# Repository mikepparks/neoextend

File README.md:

# NEOExtend
Neo Geo/Supergun compatible breakouts for arcade controls.

# Description
This series of boards is intended to help arcade controller & fighting game stick builders create a compatible interface with both the Neo Geo console/arcade platform, as well as to interface with arcade superguns that use the Neo Geo-style controller port as an input method.

Each board variation will be accompanied by a KiCad project, complete with schematic and board designs, as well as a suggested bill of materials.

# Variations
* [DB-15/DA-15](db15)
  * Intended for simplest interface between controls and system hardware.
* HD-15 (In Progress)
  * Smaller form of the DB-15 interface using a VGA-style connector. Intended for configurations where space is limited.
* DB-25 (In Progress)
  * Pin compatible with DB-15 interface, but includes access for all harness options.

# Technical Details
The NEOExtend boards are designed to use a standard 20 pin wiring harness, typically used in the creation and modification of arcade style controllers for various platforms.

The mapping of controls on these boards makes the assumption that the device is compatible with the [Undamned UD-USB Decoder](http://udgametech.blogspot.com/) pinout specification. Other specifications, such as HAS or JNX, can be supported via board or cable modifications. Depending on the board variation being used, not all inputs will be available. View the README for the desired board variation for further details.

Note: When using any of these boards on a Neo Geo platform specifically, due to the Undamned specification, be aware that the control configuration will map the _K1_ input from the arcade harness as the Neo Geo _D_ input.

Each variation of the NEOExtend board contains two 20 pin wiring harness connections to allow for daisy-chaining with existing input control hardware for compatibility with existing configurations.

# License & Usage

The NEOExtend board designs are being released to the public in hopes that they will be adapted, remixed, sold, given as tribute to the Black Magic Smoke deities, or whatever else may be done with them. However they are used, attribution is suggested, but not required.

The creator assumes no responsibility for any hardware damage that may result from using these designs.

> Creator Note: I would love to know how these designs are being used. Whenever these designs are used, please feel free to link back to the project.

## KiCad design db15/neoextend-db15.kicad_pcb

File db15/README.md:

# NEOExtend DB15
Neo Geo/Supergun compatible breakouts for arcade controls using the DB-15/DA-15 connector.

# Project Description
Refer to the main directory of the project for a summary of the complete series of boards, as well as the base usage requirements.

# Description
This variation of the NEOExtend board is intended for simplest interface between controls and system hardware. It provides access to nearly all inputs available on the 20 pin arcade harness for both Neo Geo platforms and arcade superguns that use the Neo Geo style connector for input devices.

# Recommended Bill of Materials
* 1 [Right-angle DA-15 connector with sockets](https://www.digikey.com/product-detail/en/amphenol-icc-fci/ID15S33E4GX00LF/609-5919-ND/1539017)
* 2 [20 pin header connector](https://www.digikey.com/product-detail/en/3m/30320-6002HB/3M11932-ND/1237399)

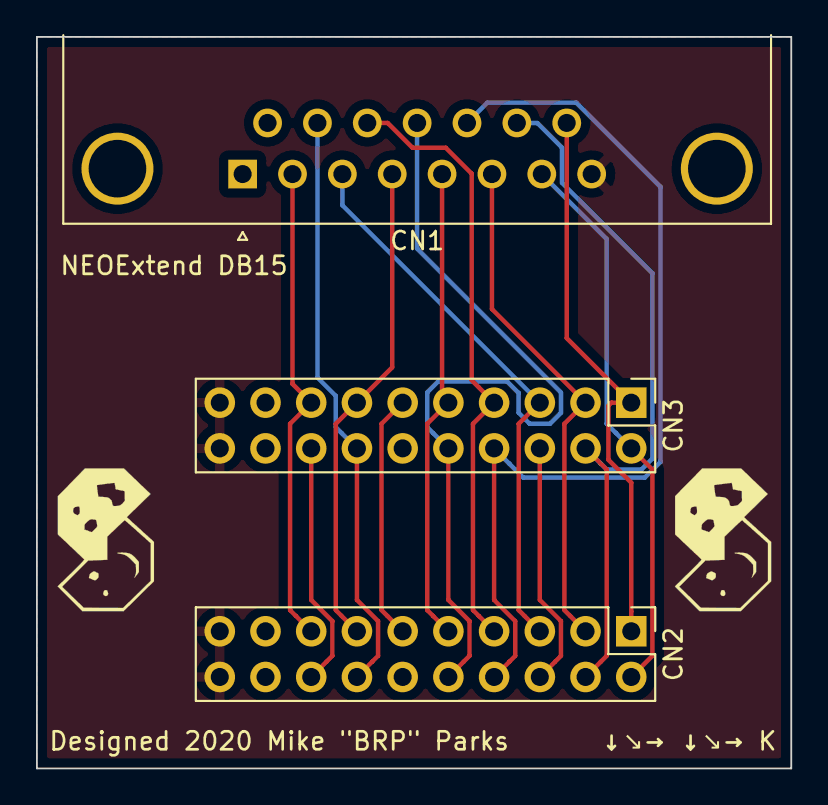
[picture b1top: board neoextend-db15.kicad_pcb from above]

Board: 2 copper layers, 41.9 x 40.6 mm, 3 parts (0 on the bottom side), 17 nets.

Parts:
CN1: DB15_Female; DSUB-15_Female_Horizontal_P2.77x2.84mm_EdgePinOffset4.94mm_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
CN2: In 2x10; PinHeader_2x10_P2.54mm_Vertical
CN3: Out 2x10; PinHeader_2x10_P2.54mm_Vertical

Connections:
/1K: CN1.4, CN2.13, CN3.13
/1P: CN1.13, CN2.8, CN3.8
/2K: CN1.10, CN2.14, CN3.14
/2P: CN1.5, CN2.9, CN3.9
/3K: CN1.2, CN2.15, CN3.15
/3P: CN1.12, CN2.10, CN3.10
/4K: CN2.16, CN3.16
/4P: CN2.11, CN3.11
/DOWN: CN1.7, CN2.2, CN3.2
/GND: CN1.1, CN2.12, CN2.17, CN2.18, CN3.12, CN3.17, CN3.18
/HOME: CN2.6, CN3.6
/LEFT: CN1.14, CN2.4, CN3.4
/RIGHT: CN1.6, CN2.3, CN3.3
/SELECT: CN1.3, CN2.5, CN3.5
/START: CN1.11, CN2.7, CN3.7
/UP: CN1.15, CN2.1, CN3.1
/VCC: CN1.8, CN2.19, CN2.20, CN3.19, CN3.20

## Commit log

2020-07-05 Initial commit.
2020-07-05 Initial commit of DB-15 Kicad project.
2020-07-05 Main summary README.
2020-07-05 Updated README to show correct view for Undamned pinout reference.
2020-07-05 Update main README with daisy-chaining details.
2020-07-05 Add DB-15 README.
2020-07-05 Update formatting on DB15 BOM.
